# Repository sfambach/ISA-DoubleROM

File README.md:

# ISA Doubel Rom 
PCB for the ISA Bus with sockets for (E)PROMS either 64 KBit or 256KBit Rom.

forked froma <a href="https://github.com/monotech/ISA-DoubleROM"> monotech/ISA-DoubleROM </a>

## Known working (E)PROMS
* 26C64 (8K)
* 27C256  (32K)
* 28C64 only reading (8K)
* 28C64B(8K)
* 38C256  (32K)

Build Confirmed to work
* 1.0 Original Monotec is working
* 1.1 Minor changes, not confirmed until now.

## Change Log
26.06.2026 - Text on PCB 256K corrected to 32K and new fabrication files generated

## Credits
*Initial Design by Monotec (Thanks to them by there work on there Website)
*Minor Changes by me. Visit my Website if you want http://www.fambach.net

## License
The intial work was distributed under the GPL3 License and so is this project, too.
Licencense Text can be found here:
https://github.com/sfambach/ISA-DoubleROM/blob/master/LICENSE

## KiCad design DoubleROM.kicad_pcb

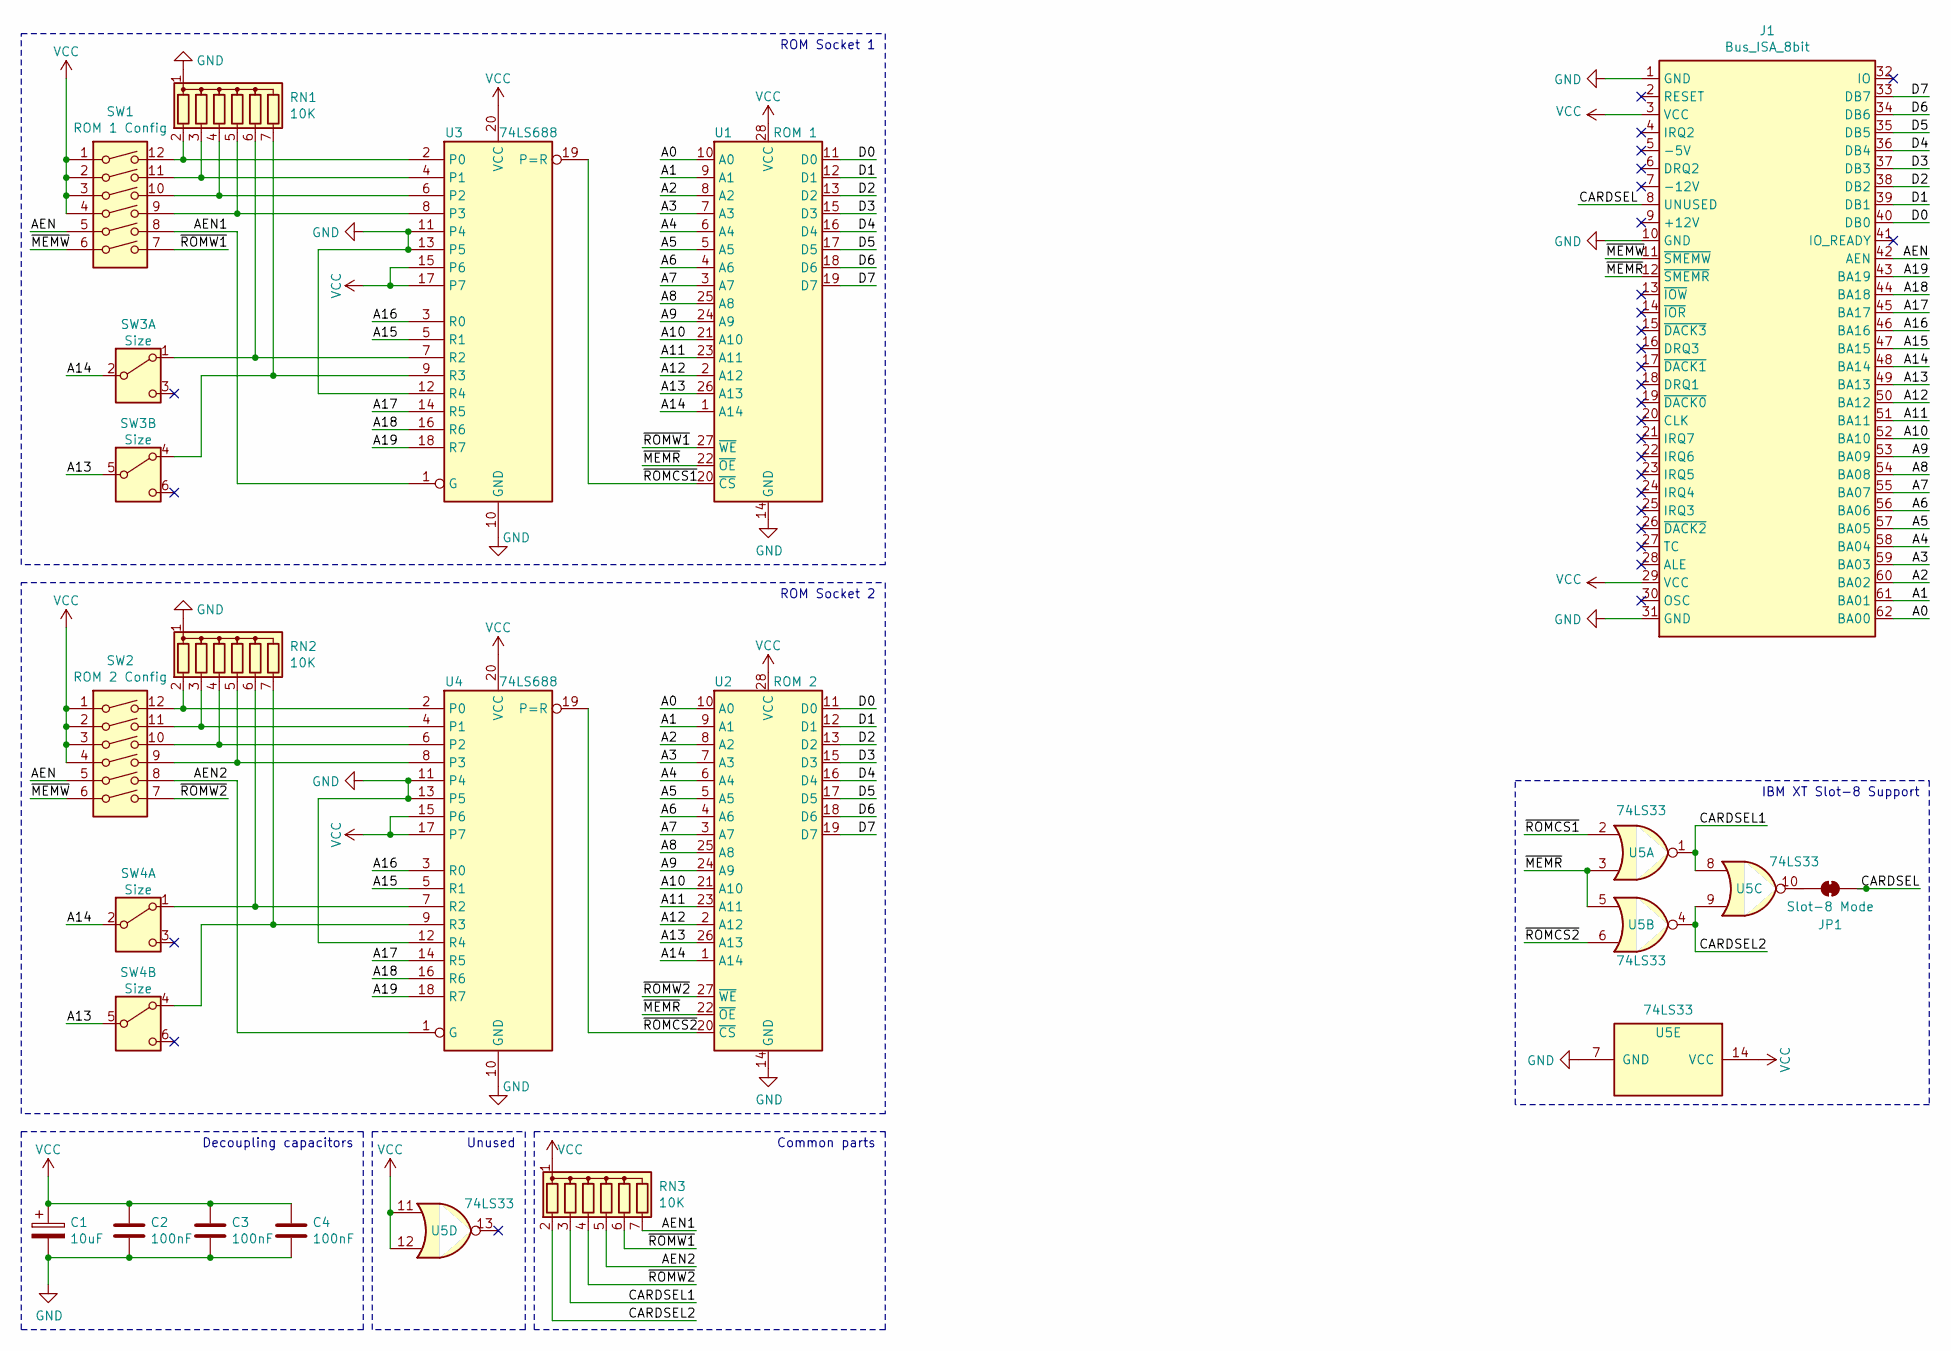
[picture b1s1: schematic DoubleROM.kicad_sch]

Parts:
C1: 10uF; CP_Radial_Tantal_D4.5mm_P5.00mm
C2, C3, C4: 100nF; C_Disc_D4.3mm_W1.9mm_P5.00mm
J1: Bus_ISA_8bit; Conn_Bus_ISA8
JP1: Slot-8 Mode; SolderJumper-2_P1.3mm_Bridged_RoundedPad1.0x1.5mm
RN1, RN2, RN3: 10K; R_Array_SIP7
SW1: ROM 1 Config; SW_DIP_SPSTx06_Slide_9.78x17.42mm_W7.62mm_P2.54mm
SW2: ROM 2 Config; SW_DIP_SPSTx06_Slide_9.78x17.42mm_W7.62mm_P2.54mm
SW3, SW4: Size; SW_MS-22D18G2
U1: ROM 1; DIP-28_W15.24mm_Socket
U2: ROM 2; DIP-28_W15.24mm_Socket
U3, U4: 74LS688; DIP-20_W7.62mm
U5: 74LS33; SOIC-14_3.9x8.7mm_P1.27mm

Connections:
/A0: J1.62 (BA00), U1.10 (A0), U2.10 (A0)
/A1: J1.61 (BA01), U1.9 (A1), U2.9 (A1)
/A2: J1.60 (BA02), U1.8 (A2), U2.8 (A2)
/A3: J1.59 (BA03), U1.7 (A3), U2.7 (A3)
/A4: J1.58 (BA04), U1.6 (A4), U2.6 (A4)
/A5: J1.57 (BA05), U1.5 (A5), U2.5 (A5)
/A6: J1.56 (BA06), U1.4 (A6), U2.4 (A6)
/A7: J1.55 (BA07), U1.3 (A7), U2.3 (A7)
/A8: J1.54 (BA08), U1.25 (A8), U2.25 (A8)
/A9: J1.53 (BA09), U1.24 (A9), U2.24 (A9)
/A10: J1.52 (BA10), U1.21 (A10), U2.21 (A10)
/A11: J1.51 (BA11), U1.23 (A11), U2.23 (A11)
/A12: J1.50 (BA12), U1.2 (A12), U2.2 (A12)
/A13: J1.49 (BA13), SW3.5 (B), SW4.5 (B), U1.26 (A13), U2.26 (A13)
/A14: J1.48 (BA14), SW3.2 (B), SW4.2 (B), U1.1 (A14), U2.1 (A14)
/A15: J1.47 (BA15), U3.5 (R1), U4.5 (R1)
/A16: J1.46 (BA16), U3.3 (R0), U4.3 (R0)
/A17: J1.45 (BA17), U3.14 (R5), U4.14 (R5)
/A18: J1.44 (BA18), U3.16 (R6), U4.16 (R6)
/A19: J1.43 (BA19), U3.18 (R7), U4.18 (R7)
/AEN: J1.42 (AEN), SW1.5, SW2.5
/AEN1: RN3.7 (R6), SW1.8, U3.1 (G)
/AEN2: RN3.5 (R4), SW2.8, U4.1 (G)
/CARDSEL: J1.8 (UNUSED), JP1.2 (B)
/CARDSEL1: RN3.3 (R2), U5.1, U5.8
/CARDSEL2: RN3.2 (R1), U5.4, U5.9
/D0: J1.40 (DB0), U1.11 (D0), U2.11 (D0)
/D1: J1.39 (DB1), U1.12 (D1), U2.12 (D1)
/D2: J1.38 (DB2), U1.13 (D2), U2.13 (D2)
/D3: J1.37 (DB3), U1.15 (D3), U2.15 (D3)
/D4: J1.36 (DB4), U1.16 (D4), U2.16 (D4)
/D5: J1.35 (DB5), U1.17 (D5), U2.17 (D5)
/D6: J1.34 (DB6), U1.18 (D6), U2.18 (D6)
/D7: J1.33 (DB7), U1.19 (D7), U2.19 (D7)
/~MEMR: J1.12 (~SMEMR), U1.22 (~OE), U2.22 (~OE), U5.3, U5.5
/~MEMW: J1.11 (~SMEMW), SW1.6, SW2.6
/~ROMCS1: U1.20 (~CS), U3.19 (P=R), U5.2
/~ROMCS2: U2.20 (~CS), U4.19 (P=R), U5.6
/~ROMW1: RN3.6 (R5), SW1.7, U1.27 (~WE)
/~ROMW2: RN3.4 (R3), SW2.7, U2.27 (~WE)
GND: C1.2, C2.2, C3.2, C4.2, J1.1 (GND), J1.10 (GND), J1.31 (GND), RN1.1 (common), RN2.1 (common), U1.14 (GND), U2.14 (GND), U3.10 (GND), U3.11 (P4), U3.12 (R4), U3.13 (P5), U4.10 (GND), U4.11 (P4), U4.12 (R4), U4.13 (P5), U5.7 (GND)
unnamed: JP1.1 (A), U5.10
unnamed: RN1.2 (R1), SW1.12, U3.2 (P0)
unnamed: RN1.3 (R2), SW1.11, U3.4 (P1)
unnamed: RN1.4 (R3), SW1.10, U3.6 (P2)
unnamed: RN1.5 (R4), SW1.9, U3.8 (P3)
unnamed: RN1.6 (R5), SW3.1 (A), U3.7 (R2)
unnamed: RN1.7 (R6), SW3.4 (A), U3.9 (R3)
unnamed: RN2.2 (R1), SW2.12, U4.2 (P0)
unnamed: RN2.3 (R2), SW2.11, U4.4 (P1)
unnamed: RN2.4 (R3), SW2.10, U4.6 (P2)
unnamed: RN2.5 (R4), SW2.9, U4.8 (P3)
unnamed: RN2.6 (R5), SW4.1 (A), U4.7 (R2)
unnamed: RN2.7 (R6), SW4.4 (A), U4.9 (R3)
VCC: C1.1, C2.1, C3.1, C4.1, J1.3 (VCC), J1.29 (VCC), RN3.1 (common), SW1.1, SW1.2, SW1.3, SW1.4, SW2.1, SW2.2, SW2.3, SW2.4, U1.28 (VCC), U2.28 (VCC), U3.15 (P6), U3.17 (P7), U3.20 (VCC), U4.15 (P6), U4.17 (P7), U4.20 (VCC), U5.11, U5.12, U5.14 (VCC)

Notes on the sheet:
IBM XT Slot-8 Support
ROM Socket 2
ROM Socket 1
Common parts
Decoupling capacitors
Unused

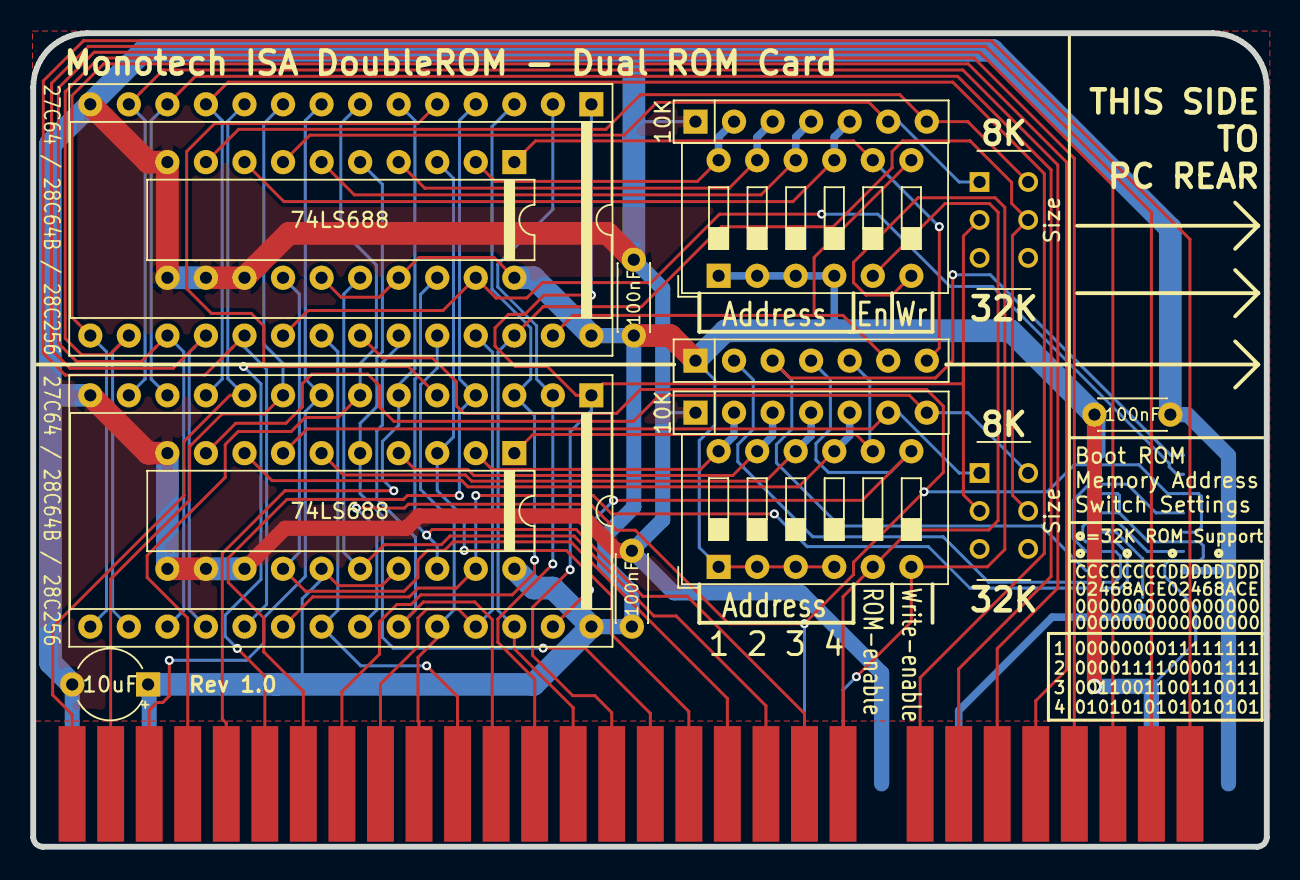
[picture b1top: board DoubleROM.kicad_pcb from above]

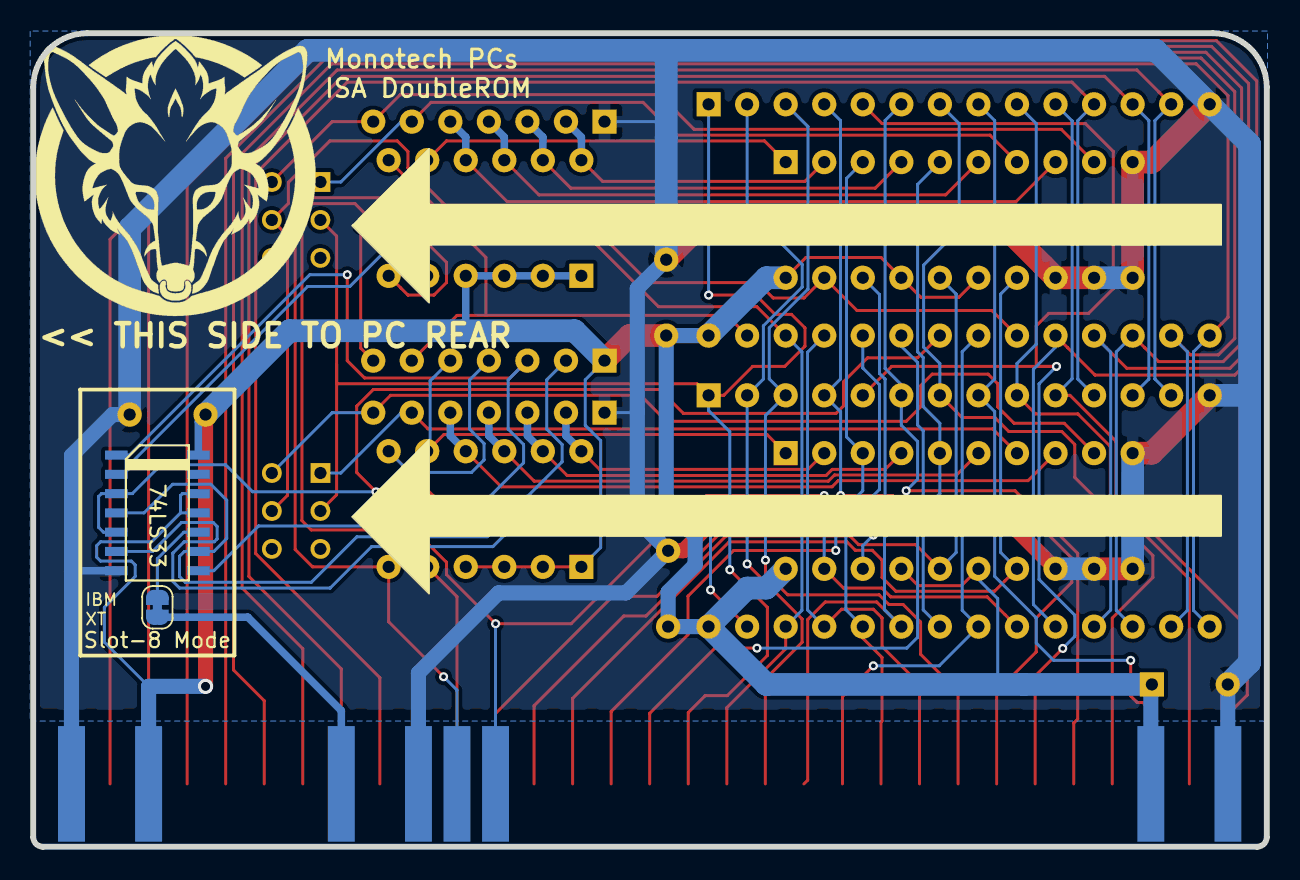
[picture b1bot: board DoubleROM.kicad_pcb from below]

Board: 2 copper layers, 81.3 x 53.6 mm, 18 parts (2 on the bottom side), 55 nets.

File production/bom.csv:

Designator,Footprint,Quantity,Value,LCSC Part #
C1,CP_Radial_Tantal_D4.5mm_P5.00mm,1,10uF,
"C2, C3, C4",C_Disc_D4.3mm_W1.9mm_P5.00mm,3,100nF,
J1,Conn_Bus_ISA8,1,Bus_ISA_8bit,
"RN1, RN2, RN3",R_Array_SIP7,3,10K,
SW1,SW_DIP_SPSTx06_Slide_9.78x17.42mm_W7.62mm_P2.54mm,1,ROM 1 Config,
SW2,SW_DIP_SPSTx06_Slide_9.78x17.42mm_W7.62mm_P2.54mm,1,ROM 2 Config,
"SW3, SW4",SW_MS-22D18G2,2,Size,
U1,DIP-28_W15.24mm_Socket,1,ROM 1,
U2,DIP-28_W15.24mm_Socket,1,ROM 2,
"U3, U4",DIP-20_W7.62mm,2,74LS688,
U5,SOIC-14_3.9x8.7mm_P1.27mm,1,74LS33,

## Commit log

2026-06-26 minor change in text 256K to 32K
